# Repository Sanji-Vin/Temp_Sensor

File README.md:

# Environmental Monitoring System  

This project is an **environmental monitoring system** built around the **ESP32-S3 Mini microcontroller**.  
It integrates multiple sensors on a custom PCB designed with **KiCad** and provides a **cross-platform monitoring application** built with **Flutter** for data visualization.  

## Features  
- 📟 **Custom PCB** with ESP32-S3 Mini, designed in KiCad  
- 🌡️ Temperature & humidity monitoring  
- 💡 Light intensity measurement  
- 🌫️ Air quality monitoring  
- 📡 Wi-Fi connectivity for real-time data transfer  
- 📊 Cross-platform Flutter app with:  
  - Interactive charts for sensor data  
  - Device status monitoring  
  - 24h data history  

## Technologies Used  
- **Hardware**:  
  - ESP32-S3 Mini  
  - I²C communication protocol  
  - KiCad for PCB design  
  - Integrated environmental sensors: -BME280 (temperature, Humidity sensor)
                                      -VEML7700(Light intensity sensor)
                                      -SGP40(air quality sensor)

- **Software**:  
  - Flutter for cross-platform app development  
  - Dart for frontend logic  
  - Charts & dashboard UI for data visualization  

## Repository  
Feel free to explore the code and design files in this repository.  
Contributions, feedback, and suggestions are always welcome! 🚀

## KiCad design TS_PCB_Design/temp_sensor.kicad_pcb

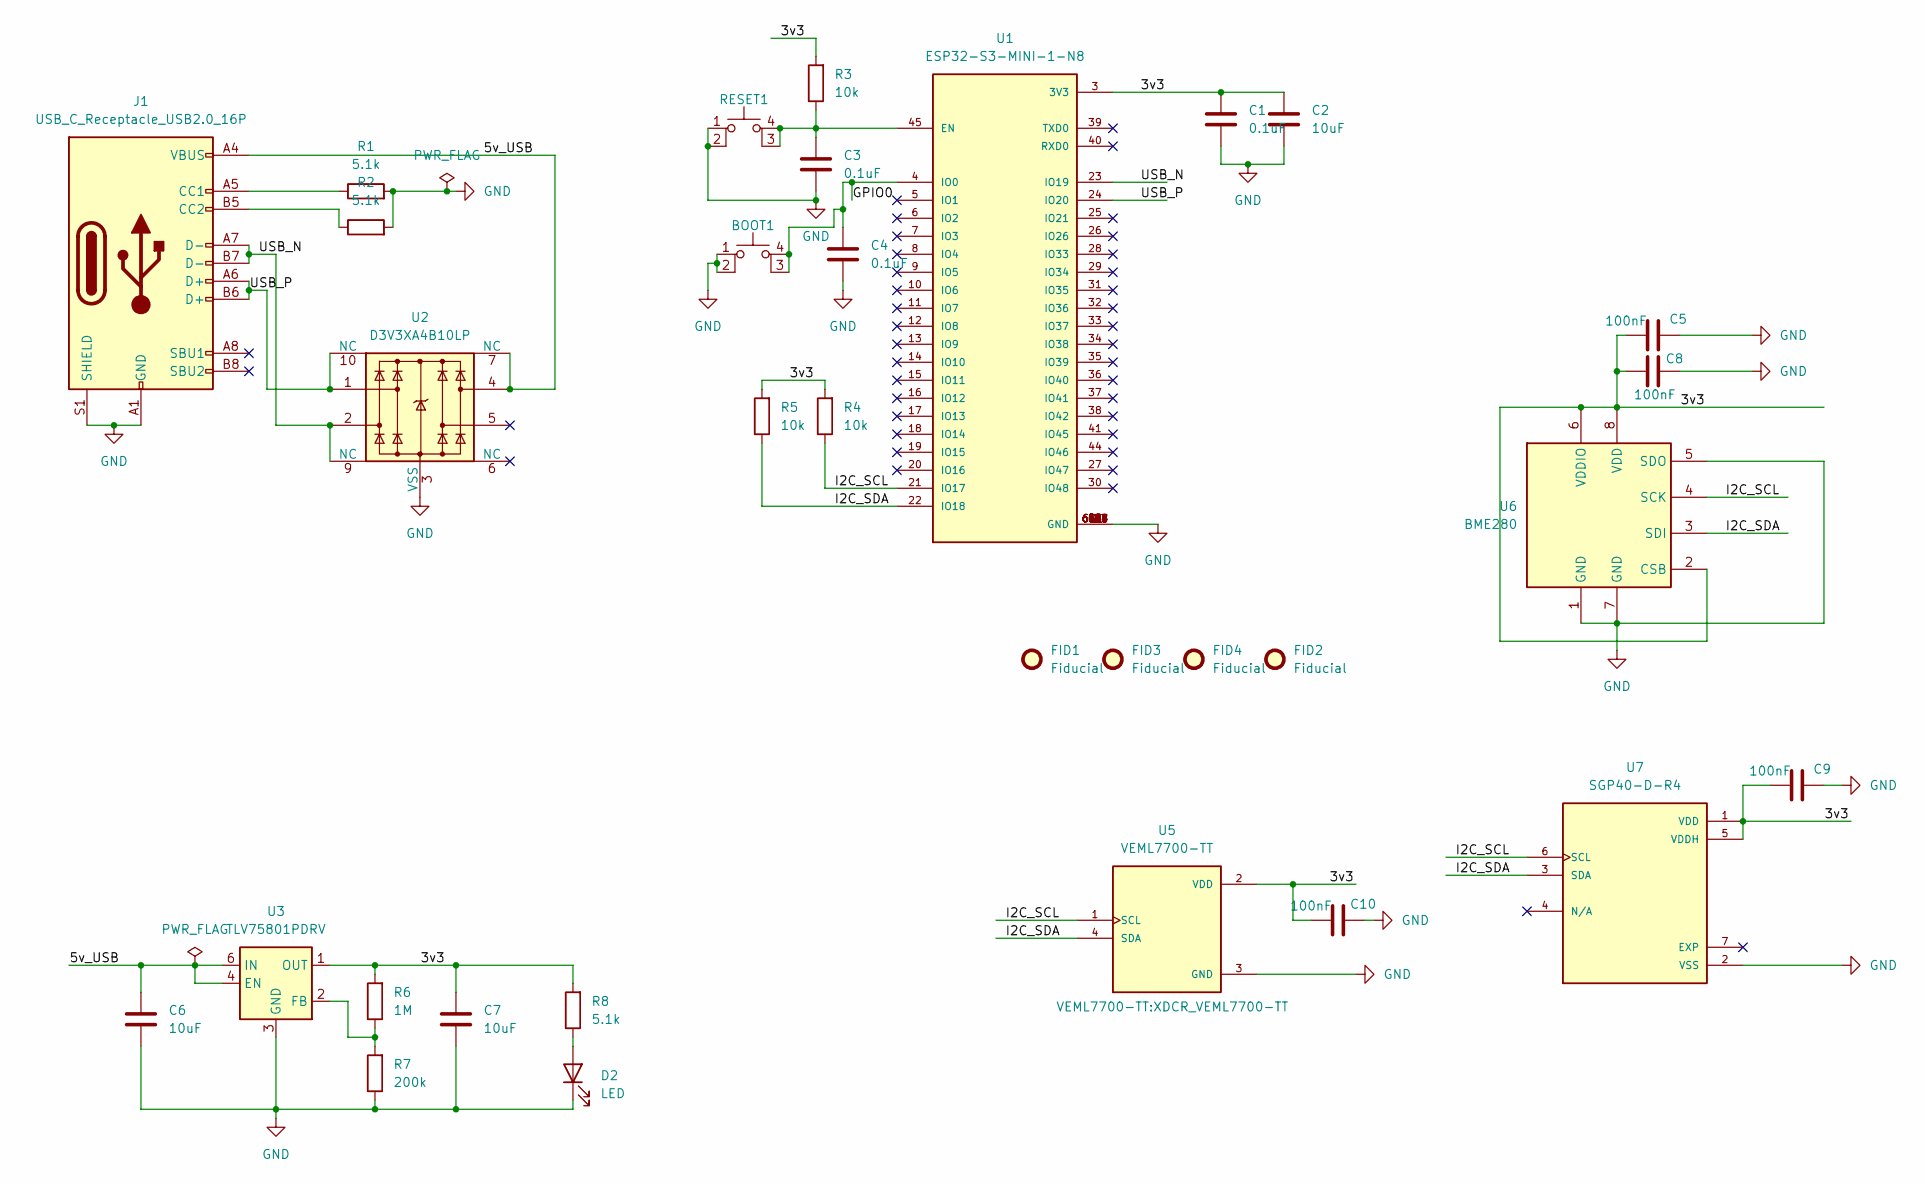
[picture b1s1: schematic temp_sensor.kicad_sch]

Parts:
BOOT1: SW_MEC_5E; SW_SPST_PTS810
C1, C3, C4: 0.1uF; C_0603_1608Metric
C2, C6, C7: 10uF; C_0603_1608Metric
C5, C8, C9, C10: 100nF; C_0603_1608Metric
D2: LED; LED_0603_1608Metric
FID1, FID2, FID3, FID4: Fiducial; Fiducial_1mm_Mask2mm
J1: USB_C_Receptacle_USB2.0_16P; USB_C_Receptacle_GCT_USB4105-xx-A_16P_TopMnt_Horizontal
R1, R2, R8: 5.1k; R_0603_1608Metric
R3, R4, R5: 10k; R_0603_1608Metric
R6: 1M; R_0603_1608Metric
R7: 200k; R_0603_1608Metric
RESET1: SW_MEC_5E; SW_SPST_PTS810
U1: ESP32-S3-MINI-1-N8; XCVR_ESP32-S3-MINI-1-N8; PARTREV v0.6
U2: D3V3XA4B10LP; Diodes_UDFN-10_1.0x2.5mm_P0.5mm
U3: TLV75801PDRV; WSON-6-1EP_2x2mm_P0.65mm_EP1x1.6mm
U5: VEML7700-TT; XDCR_VEML7700-TT; PARTREV 1.6
U6: BME280; Bosch_LGA-8_2.5x2.5mm_P0.65mm_ClockwisePinNumbering
U7: SGP40-D-R4; XCDR_SGP40-D-R4; PARTREV 1.2

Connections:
/3v3: C1.1, C2.1, C5.1, C7.1, C8.1, C9.1, C10.1, R3.2, R4.2, R5.2, R6.2, R8.2, U1.3 (3V3), U3.1 (OUT), U5.2 (VDD), U6.2 (CSB), U6.6 (VDDIO), U6.8 (VDD), U7.1 (VDD), U7.5 (VDDH)
/5v_USB: C6.1, J1.A4 (VBUS), J1.A9 (VBUS), J1.B4 (VBUS), J1.B9 (VBUS), U2.4, U2.7 (NC), U3.4 (EN), U3.6 (IN)
/GPIO0: BOOT1.3 (K), BOOT1.4 (A), C4.1, U1.4 (IO0)
/GPIO48: U1.30 (IO48)
/I2C_SCL: R4.1, U1.21 (IO17), U5.1 (SCL), U6.4 (SCK), U7.6 (SCL)
/I2C_SDA: R5.1, U1.22 (IO18), U5.4 (SDA), U6.3 (SDI), U7.3 (SDA)
/USB_N: J1.A7 (D-), J1.B7 (D-), U1.23 (IO19), U2.2, U2.9 (NC)
/USB_P: J1.A6 (D+), J1.B6 (D+), U1.24 (IO20), U2.1, U2.10 (NC)
GND: BOOT1.1, BOOT1.2, C1.2, C2.2, C3.2, C4.2, C5.2, C6.2, C7.2, C8.2, C9.2, C10.2, D2.1 (K), J1.A1 (GND), J1.A12 (GND), J1.B1 (GND), J1.B12 (GND), J1.S1 (SHIELD), R1.2, R2.2, R7.1, RESET1.1, RESET1.2, U1.1 (GND), U1.2 (GND), U1.42 (GND), U1.43 (GND), U1.46 (GND), U1.47 (GND), U1.48 (GND), U1.49 (GND), U1.50 (GND), U1.51 (GND), U1.52 (GND), U1.53 (GND), U1.54 (GND), U1.55 (GND), U1.56 (GND), U1.57 (GND), U1.58 (GND), U1.59 (GND), U1.60 (GND), U1.61 (GND), U1.61_1 (GND), U1.61_2 (GND), U1.61_3 (GND), U1.61_4 (GND), U1.61_5 (GND), U1.61_6 (GND), U1.61_7 (GND), U1.61_8 (GND), U1.62 (GND), U1.63 (GND), U1.64 (GND), U1.65 (GND), U2.3 (VSS), U2.8 (VSS), U3.3 (GND), U3.7 (GND), U5.3 (GND), U6.1 (GND), U6.5 (SDO), U6.7 (GND), U7.2 (VSS)
unnamed: D2.2 (A), R8.1
unnamed: J1.A5 (CC1), R1.1
unnamed: J1.B5 (CC2), R2.1
unnamed: C3.1, R3.1, RESET1.3 (K), RESET1.4 (A), U1.45 (EN)
unnamed: R6.1, R7.2, U3.2 (FB)

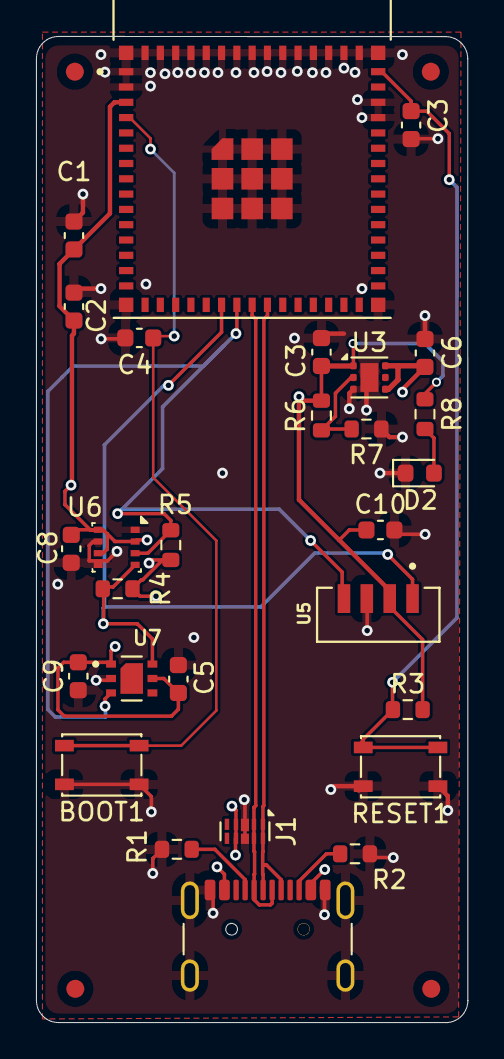
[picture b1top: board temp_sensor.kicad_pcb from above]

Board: 4 copper layers, 24.0 x 54.8 mm, 32 parts (0 on the bottom side), 13 nets.

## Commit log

2025-08-17 empty app
2025-08-18 added the pcb design
2025-08-18 updated the pubspec and constants folder
2025-08-18 started building the navbar
2025-08-18 finished the navbar and started working on the dashboard
2025-08-19 made the temp chart
2025-08-20 added humidity, light intensity and air quality charts
2025-08-20 updated the charts
2025-08-20 added the chart bars and started working on the summary widget
2025-08-20 finished the right card
2025-08-20 added libraries
